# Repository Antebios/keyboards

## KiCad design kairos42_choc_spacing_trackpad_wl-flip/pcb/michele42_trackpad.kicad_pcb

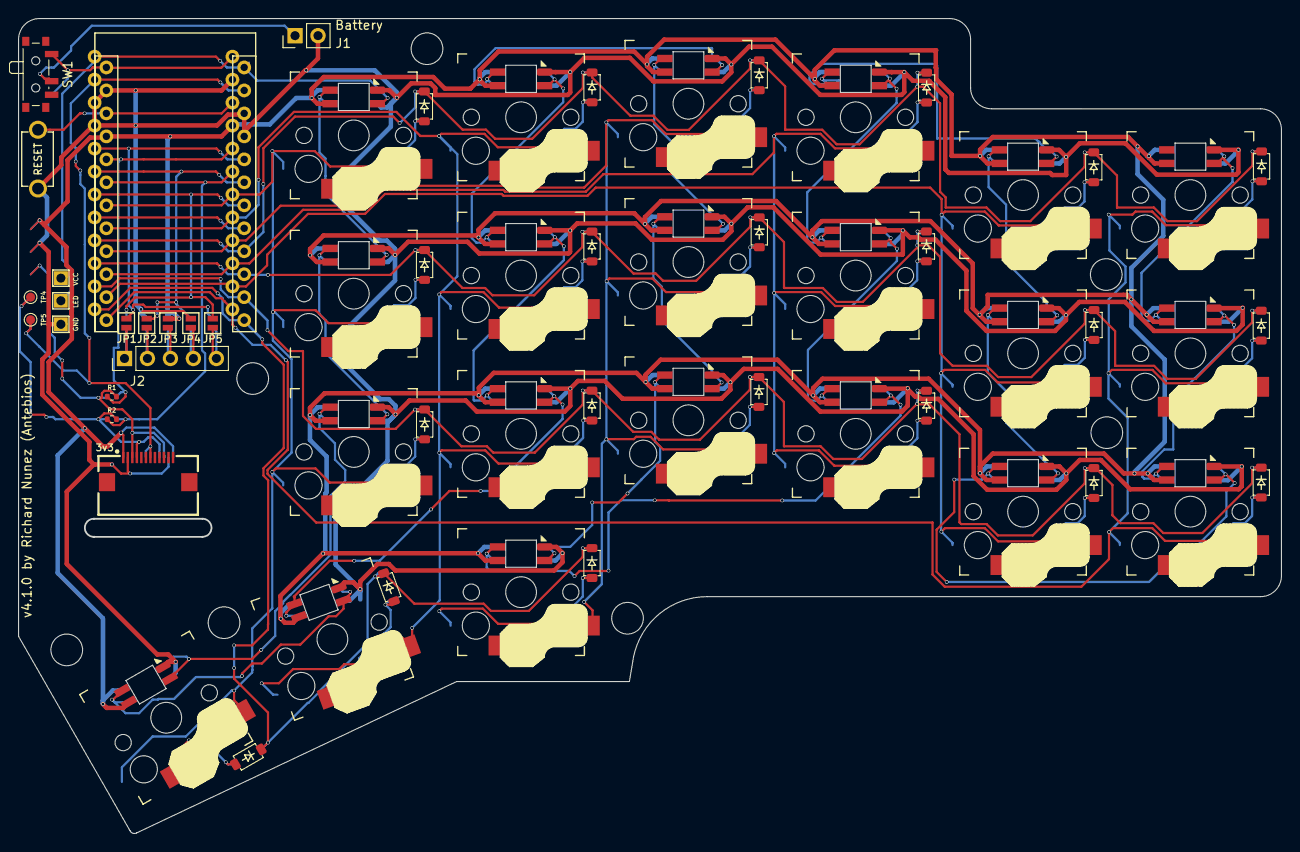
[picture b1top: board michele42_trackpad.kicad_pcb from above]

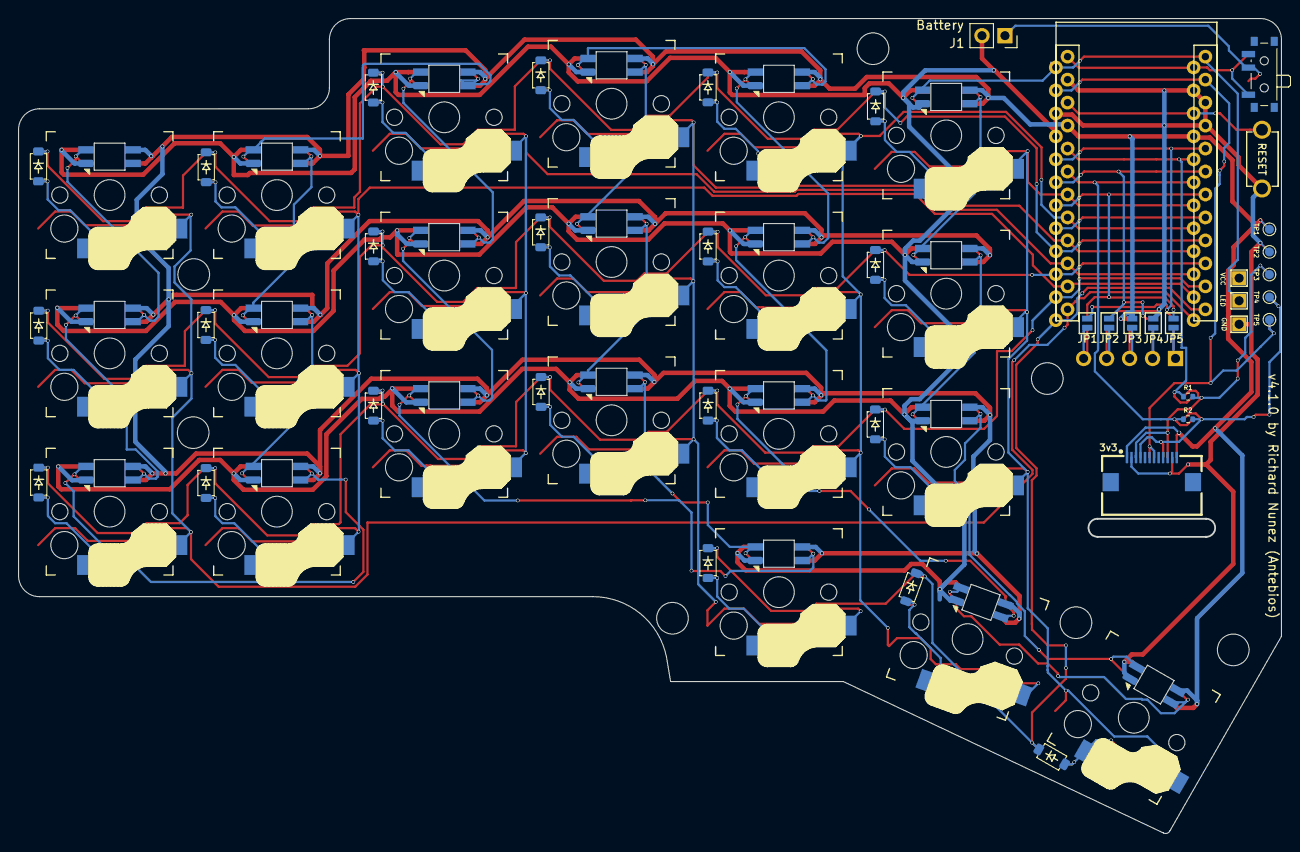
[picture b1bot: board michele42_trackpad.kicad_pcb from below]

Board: 2 copper layers, 139.5 x 90.0 mm, 99 parts (34 on the bottom side), 70 nets.

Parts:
D1, D2, D3, D4, D5, D6, D7, D8, D9, D10, D11, D12, D13, D14, D15, D16, D17, D18, D19, D20, D21: Diode; Diode_SOD-123-double-sided
D22, D23, D24, D25, D26, D27, D28, D29, D30, D31, D32, D33, D34, D35, D36, D37, D38, D39, D40, D41, D42: SK6812MINI-E; SK6812-MINI-E-double-side
H1, H2, H3, H4, H5, H6, H7: Mounting_Hole; MountingHole_3.5mm
J1: Battery; PinHeader_1x02_P2.54mm_Vertical
J2: OLED-5Pin; PinHeader_1x05_P2.54mm_Vertical
J3, J3#2: vik-keyboard-connector-horizontal
J4: LED
JP1, JP1#2, JP2, JP2#2, JP3, JP3#2, JP4, JP4#2, JP5, JP5#2: Jumper; jumper_data-MOD
R1, R1#2, R2, R2#2: 4.7k; R_0402_1005Metric
RSW1: SW_RST; TACT_SWITCH_TVBP06
S1, S2, S3, S4, S5, S6, S7, S8, S9, S10, S11, S12, S13, S14, S15, S16, S17, S18, S19, S20, S21: Keyswitch; Choc_Hotswap-double-sided
SW1: SW_Power; SW_SPDT_PCM12
TP1, TP2, TP3, TP4, TP4#2, TP5, TP5#2: TestPoint; TestPoint_Pad_D1.0mm
U1: MCU_Nice_Nano_V2; ProMicro

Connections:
BATTERY: SW1.1 (A), U1.24 (B+)
CS: JP5.2 (B), JP5#2.2 (B), U1.7 (D4)
Column 0: S1.2, S7.2, S13.2, S19.2, U1.18 (D19)
Column 1: S2.2, S8.2, S14.2, S20.2, U1.17 (D18)
Column 2: S3.2, S9.2, S15.2, S21.2, U1.16 (D15)
Column 3: S4.2, S10.2, S16.2, U1.15 (D14)
Column 4: S5.2, S11.2, S17.2, U1.14 (D16)
Column 5: S6.2, S12.2, S18.2, U1.13 (D10)
DRDY: J3.7 (GP_AD1), J3#2.7 (GP_AD1), TP5.1 (1_1), TP5#2.1 (1_1), U1.2 (D0)
GND: D22.3 (GND), D23.3 (GND), D24.3 (GND), D25.3 (GND), D26.3 (GND), D27.3 (GND), D28.3 (GND), D29.3 (GND), D30.3 (GND), D31.3 (GND), D32.3 (GND), D33.3 (GND), D34.3 (GND), D35.3 (GND), D36.3 (GND), D37.3 (GND), D38.3 (GND), D39.3 (GND), D40.3 (GND), D41.3 (GND), D42.3 (GND), J1.2, J3.2 (GND), J3#2.2 (GND), J4.3, JP4.2 (B), JP4#2.2 (B), RSW1.1, TP2.1 (1_1), U1.3 (GND), U1.4 (GND), U1.23 (GND)
LED: D22.4 (DIN), J4.2, U1.1 (D1)
MOSI: JP1.2 (B), JP1#2.2 (B), U1.5 (D2)
unnamed: D1.2 (A), S1.1
unnamed: D2.2 (A), S2.1
unnamed: D3.2 (A), S3.1
unnamed: D4.2 (A), S4.1
unnamed: D5.2 (A), S5.1
unnamed: D6.2 (A), S6.1
unnamed: D7.2 (A), S7.1
unnamed: D8.2 (A), S8.1
unnamed: D9.2 (A), S9.1
unnamed: D10.2 (A), S10.1
unnamed: D11.2 (A), S11.1
unnamed: D12.2 (A), S12.1
unnamed: D13.2 (A), S13.1
unnamed: D14.2 (A), S14.1
unnamed: D15.2 (A), S15.1
unnamed: D16.2 (A), S16.1
unnamed: D17.2 (A), S17.1
unnamed: D18.2 (A), S18.1
unnamed: D19.2 (A), S19.1
unnamed: D20.2 (A), S20.1
unnamed: D21.2 (A), S21.1
unnamed: D22.2 (DOUT), D28.4 (DIN)
unnamed: D23.4 (DIN), D29.2 (DOUT)
unnamed: D23.2 (DOUT), D24.4 (DIN)
unnamed: D24.2 (DOUT), D30.4 (DIN)
unnamed: D25.4 (DIN), D31.2 (DOUT)
unnamed: D25.2 (DOUT), D26.4 (DIN)
unnamed: D26.2 (DOUT), D32.4 (DIN)
unnamed: D27.4 (DIN), D33.2 (DOUT)
unnamed: D28.2 (DOUT), D34.4 (DIN)
unnamed: D29.4 (DIN), D35.2 (DOUT)
unnamed: D30.2 (DOUT), D36.4 (DIN)
unnamed: D31.4 (DIN), D37.2 (DOUT)
unnamed: D32.2 (DOUT), D38.4 (DIN)
unnamed: D33.4 (DIN), D39.2 (DOUT)
unnamed: D34.2 (DOUT), D40.4 (DIN)
unnamed: D35.4 (DIN), D41.2 (DOUT)
unnamed: D36.2 (DOUT), D42.4 (DIN)
unnamed: D37.4 (DIN), D42.2 (DOUT)
unnamed: D38.2 (DOUT), D39.4 (DIN)
unnamed: D40.2 (DOUT), D41.4 (DIN)
unnamed: J1.1, SW1.2 (B)
unnamed: J2.1, JP1.1 (A), JP5#2.1 (A)
unnamed: J2.2, JP2.1 (A), JP4#2.1 (A)
unnamed: J2.3, JP3.1 (A), JP3#2.1 (A)
unnamed: J2.4, JP2#2.1 (A), JP4.1 (A)
unnamed: J2.5, JP1#2.1 (A), JP5.1 (A)
RESET: RSW1.2, U1.22 (RST)
Row 0: D1.1 (K), D2.1 (K), D3.1 (K), D4.1 (K), D5.1 (K), D6.1 (K), U1.9 (D6)
Row 1: D7.1 (K), D8.1 (K), D9.1 (K), D10.1 (K), D11.1 (K), D12.1 (K), U1.10 (D7)
Row 2: D13.1 (K), D14.1 (K), D15.1 (K), D16.1 (K), D17.1 (K), D18.1 (K), U1.11 (D8)
Row 3: D19.1 (K), D20.1 (K), D21.1 (K), U1.12 (D9)
SCK: JP2.2 (B), JP2#2.2 (B), U1.6 (D3)
SCL: R2.1, R2#2.1, U1.19 (D20)
SDA: R1.1, R1#2.1, U1.20 (D21)
TP-SCL: J3.4 (SCL), J3#2.4 (SCL), R2.2, R2#2.2, TP4.1 (1_1), TP4#2.1 (1_1)
TP-SDA: J3.3 (SDA), J3#2.3 (SDA), R1.2, R1#2.2, TP3.1 (1_1)
VCC: D22.1 (VDD), D23.1 (VDD), D24.1 (VDD), D25.1 (VDD), D26.1 (VDD), D27.1 (VDD), D28.1 (VDD), D29.1 (VDD), D30.1 (VDD), D31.1 (VDD), D32.1 (VDD), D33.1 (VDD), D34.1 (VDD), D35.1 (VDD), D36.1 (VDD), D37.1 (VDD), D38.1 (VDD), D39.1 (VDD), D40.1 (VDD), D41.1 (VDD), D42.1 (VDD), J3.1 (3V3), J3#2.1 (3V3), J4.1, JP3.2 (B), JP3#2.2 (B), TP1.1 (1_1), U1.21 (3.3v)

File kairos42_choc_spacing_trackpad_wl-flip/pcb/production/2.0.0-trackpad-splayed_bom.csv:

Designator,Footprint,Quantity,Value,LCSC Part #
"D1, D10, D11, D12, D13, D14, D15, D16, D17, D18, D19, D2, D20, D21, D22, D3, D4, D5, D6, D7, D8, D9",SK6812-MINI-E-double-side,22,SK6812MINI-E,
"D23, D24, D25, D26, D27, D28, D29, D30, D31, D32, D33, D34, D35, D36, D37, D38, D39, D40, D41, D42, D43, D44",Diode_SOD-123-double-sided,22,Diode,
"H1, H2, H3, H4, H5, H6, H7",MountingHole_3.5mm,7,Mounting_Hole,
J1,PinHeader_1x02_P2.54mm_Vertical,1,Battery,
"J2, J3",vik-keyboard-connector-horizontal,2,~,
J3_2,PinHeader_1x05_P2.54mm_Vertical,1,OLED-5Pin,
J4,LED,1,LED,
"JP1_2, JP1, JP2_2, JP2, JP3_2, JP3, JP4_2, JP4, JP5_2, JP5",jumper_data-MOD,10,Jumper,
"R1_2, R1, R2_2, R2",0402,4,4.7k,
RSW1,TACT_SWITCH_TVBP06,1,SW_RST,
"S1, S10, S11, S12, S13, S14, S15, S16, S17, S18, S19, S2, S20, S21, S22, S3, S4, S5, S6, S7, S8, S9",Choc_Hotswap-double-sided,22,Keyswitch,
SW1,SW_SPDT_PCM12,1,SW_Power,
"TP1_2, TP1, TP2_2, TP2, TP3_2, TP3, TP4_2, TP4, TP5_2, TP5",TestPoint_Pad_D1.0mm,10,TestPoint,
U1,ProMicro,1,MCU_Nice_Nano_V2,

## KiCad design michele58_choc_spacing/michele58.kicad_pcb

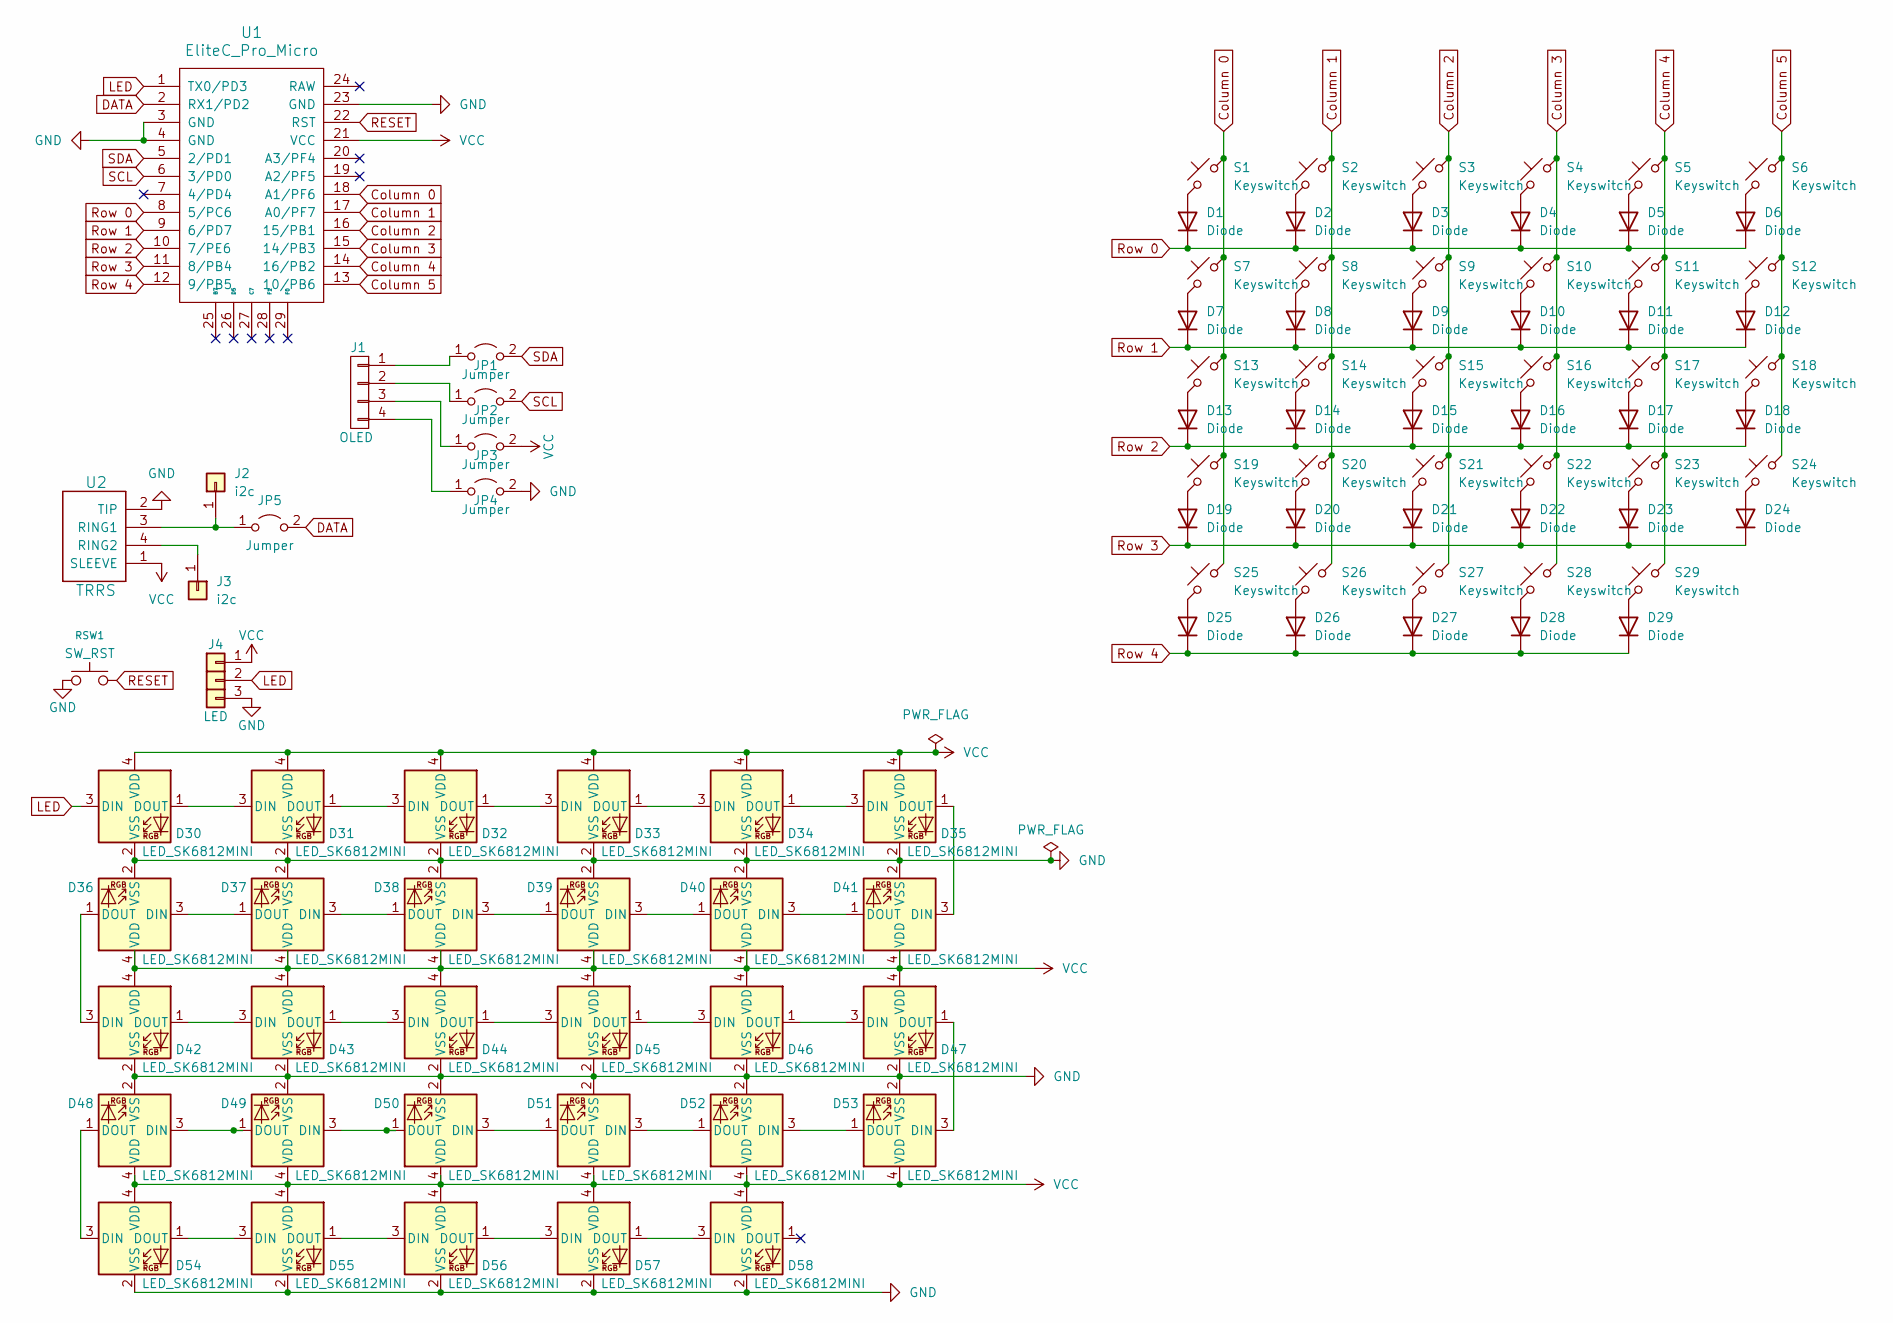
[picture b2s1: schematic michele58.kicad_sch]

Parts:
D1, D2, D3, D4, D5, D6, D7, D8, D9, D10, D11, D12, D13, D14, D15, D16, D17, D18, D19, D20, D21, D22, D23, D24, D25, D26, D27, D28, D29: Diode; Diode_SOD-123
D30, D31, D32, D33, D34, D35, D36, D37, D38, D39, D40, D41, D42, D43, D44, D45, D46, D47, D48, D49, D50, D51, D52, D53, D54, D55, D56, D57, D58: LED_SK6812MINI; LED_SK6812MINI-MOD1
J1: OLED; OLED_4Pin
J2, J3: i2c; 1pin_conn
J4: LED
JP1, JP2, JP3, JP4, JP5: Jumper; jumper_data-MOD
RSW1: SW_RST; TACT_SWITCH_TVBP06
S1, S2, S3, S4, S5, S6, S7, S8, S9, S10, S11, S12, S13, S14, S15, S16, S17, S18, S19, S20, S21, S22, S23, S24, S25, S26, S27, S28, S29: Keyswitch; SW_Kailh_Choc_V1_1.00u
U1: EliteC_Pro_Micro; Elite-C
U2: TRRS; TRRS_PJ-320A

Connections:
Column 0: S1.2, S7.2, S13.2, S19.2, S25.2, U1.18 (A1/PF6)
Column 1: S2.2, S8.2, S14.2, S20.2, S26.2, U1.17 (A0/PF7)
Column 2: S3.2, S9.2, S15.2, S21.2, S27.2, U1.16 (15/PB1)
Column 3: S4.2, S10.2, S16.2, S22.2, S28.2, U1.15 (14/PB3)
Column 4: S5.2, S11.2, S17.2, S23.2, S29.2, U1.14 (16/PB2)
Column 5: S6.2, S12.2, S18.2, S24.2, U1.13 (10/PB6)
DATA: JP5.2 (B), U1.2 (RX1/PD2)
GND: D30.2 (VSS), D31.2 (VSS), D32.2 (VSS), D33.2 (VSS), D34.2 (VSS), D35.2 (VSS), D36.2 (VSS), D37.2 (VSS), D38.2 (VSS), D39.2 (VSS), D40.2 (VSS), D41.2 (VSS), D42.2 (VSS), D43.2 (VSS), D44.2 (VSS), D45.2 (VSS), D46.2 (VSS), D47.2 (VSS), D48.2 (VSS), D49.2 (VSS), D50.2 (VSS), D51.2 (VSS), D52.2 (VSS), D53.2 (VSS), D54.2 (VSS), D55.2 (VSS), D56.2 (VSS), D57.2 (VSS), D58.2 (VSS), J4.3, JP4.2 (B), RSW1.1, U1.3 (GND), U1.4 (GND), U1.23 (GND), U2.2 (TIP)
LED: D30.3 (DIN), J4.2, U1.1 (TX0/PD3)
unnamed: D1.2 (A), S1.1
unnamed: D2.2 (A), S2.1
unnamed: D3.2 (A), S3.1
unnamed: D4.2 (A), S4.1
unnamed: D5.2 (A), S5.1
unnamed: D6.2 (A), S6.1
unnamed: D7.2 (A), S7.1
unnamed: D8.2 (A), S8.1
unnamed: D9.2 (A), S9.1
unnamed: D10.2 (A), S10.1
unnamed: D11.2 (A), S11.1
unnamed: D12.2 (A), S12.1
unnamed: D13.2 (A), S13.1
unnamed: D14.2 (A), S14.1
unnamed: D15.2 (A), S15.1
unnamed: D16.2 (A), S16.1
unnamed: D17.2 (A), S17.1
unnamed: D18.2 (A), S18.1
unnamed: D19.2 (A), S19.1
unnamed: D20.2 (A), S20.1
unnamed: D21.2 (A), S21.1
unnamed: D22.2 (A), S22.1
unnamed: D23.2 (A), S23.1
unnamed: D24.2 (A), S24.1
unnamed: D25.2 (A), S25.1
unnamed: D26.2 (A), S26.1
unnamed: D27.2 (A), S27.1
unnamed: D28.2 (A), S28.1
unnamed: D29.2 (A), S29.1
unnamed: D30.1 (DOUT), D31.3 (DIN)
unnamed: D31.1 (DOUT), D32.3 (DIN)
unnamed: D32.1 (DOUT), D33.3 (DIN)
unnamed: D33.1 (DOUT), D34.3 (DIN)
unnamed: D34.1 (DOUT), D35.3 (DIN)
unnamed: D35.1 (DOUT), D41.3 (DIN)
unnamed: D36.3 (DIN), D37.1 (DOUT)
unnamed: D36.1 (DOUT), D42.3 (DIN)
unnamed: D37.3 (DIN), D38.1 (DOUT)
unnamed: D38.3 (DIN), D39.1 (DOUT)
unnamed: D39.3 (DIN), D40.1 (DOUT)
unnamed: D40.3 (DIN), D41.1 (DOUT)
unnamed: D42.1 (DOUT), D43.3 (DIN)
unnamed: D43.1 (DOUT), D44.3 (DIN)
unnamed: D44.1 (DOUT), D45.3 (DIN)
unnamed: D45.1 (DOUT), D46.3 (DIN)
unnamed: D46.1 (DOUT), D47.3 (DIN)
unnamed: D47.1 (DOUT), D53.3 (DIN)
unnamed: D48.3 (DIN), D49.1 (DOUT)
unnamed: D48.1 (DOUT), D54.3 (DIN)
unnamed: D49.3 (DIN), D50.1 (DOUT)
unnamed: D50.3 (DIN), D51.1 (DOUT)
unnamed: D51.3 (DIN), D52.1 (DOUT)
unnamed: D52.3 (DIN), D53.1 (DOUT)
unnamed: D54.1 (DOUT), D55.3 (DIN)
unnamed: D55.1 (DOUT), D56.3 (DIN)
unnamed: D56.1 (DOUT), D57.3 (DIN)
unnamed: D57.1 (DOUT), D58.3 (DIN)
unnamed: J1.1, JP1.1 (A)
unnamed: J1.2, JP2.1 (A)
unnamed: J1.3, JP3.1 (A)
unnamed: J1.4, JP4.1 (A)
unnamed: J2.1, JP5.1 (A), U2.3 (RING1)
unnamed: J3.1, U2.4 (RING2)
RESET: RSW1.2, U1.22 (RST)
Row 0: D1.1 (K), D2.1 (K), D3.1 (K), D4.1 (K), D5.1 (K), D6.1 (K), U1.8 (5/PC6)
Row 1: D7.1 (K), D8.1 (K), D9.1 (K), D10.1 (K), D11.1 (K), D12.1 (K), U1.9 (6/PD7)
Row 2: D13.1 (K), D14.1 (K), D15.1 (K), D16.1 (K), D17.1 (K), D18.1 (K), U1.10 (7/PE6)
Row 3: D19.1 (K), D20.1 (K), D21.1 (K), D22.1 (K), D23.1 (K), D24.1 (K), U1.11 (8/PB4)
Row 4: D25.1 (K), D26.1 (K), D27.1 (K), D28.1 (K), D29.1 (K), U1.12 (9/PB5)
SCL: JP2.2 (B), U1.6 (3/PD0)
SDA: JP1.2 (B), U1.5 (2/PD1)
VCC: D30.4 (VDD), D31.4 (VDD), D32.4 (VDD), D33.4 (VDD), D34.4 (VDD), D35.4 (VDD), D36.4 (VDD), D37.4 (VDD), D38.4 (VDD), D39.4 (VDD), D40.4 (VDD), D41.4 (VDD), D42.4 (VDD), D43.4 (VDD), D44.4 (VDD), D45.4 (VDD), D46.4 (VDD), D47.4 (VDD), D48.4 (VDD), D49.4 (VDD), D50.4 (VDD), D51.4 (VDD), D52.4 (VDD), D53.4 (VDD), D54.4 (VDD), D55.4 (VDD), D56.4 (VDD), D57.4 (VDD), D58.4 (VDD), J4.1, JP3.2 (B), U1.21 (VCC), U2.1 (SLEEVE)

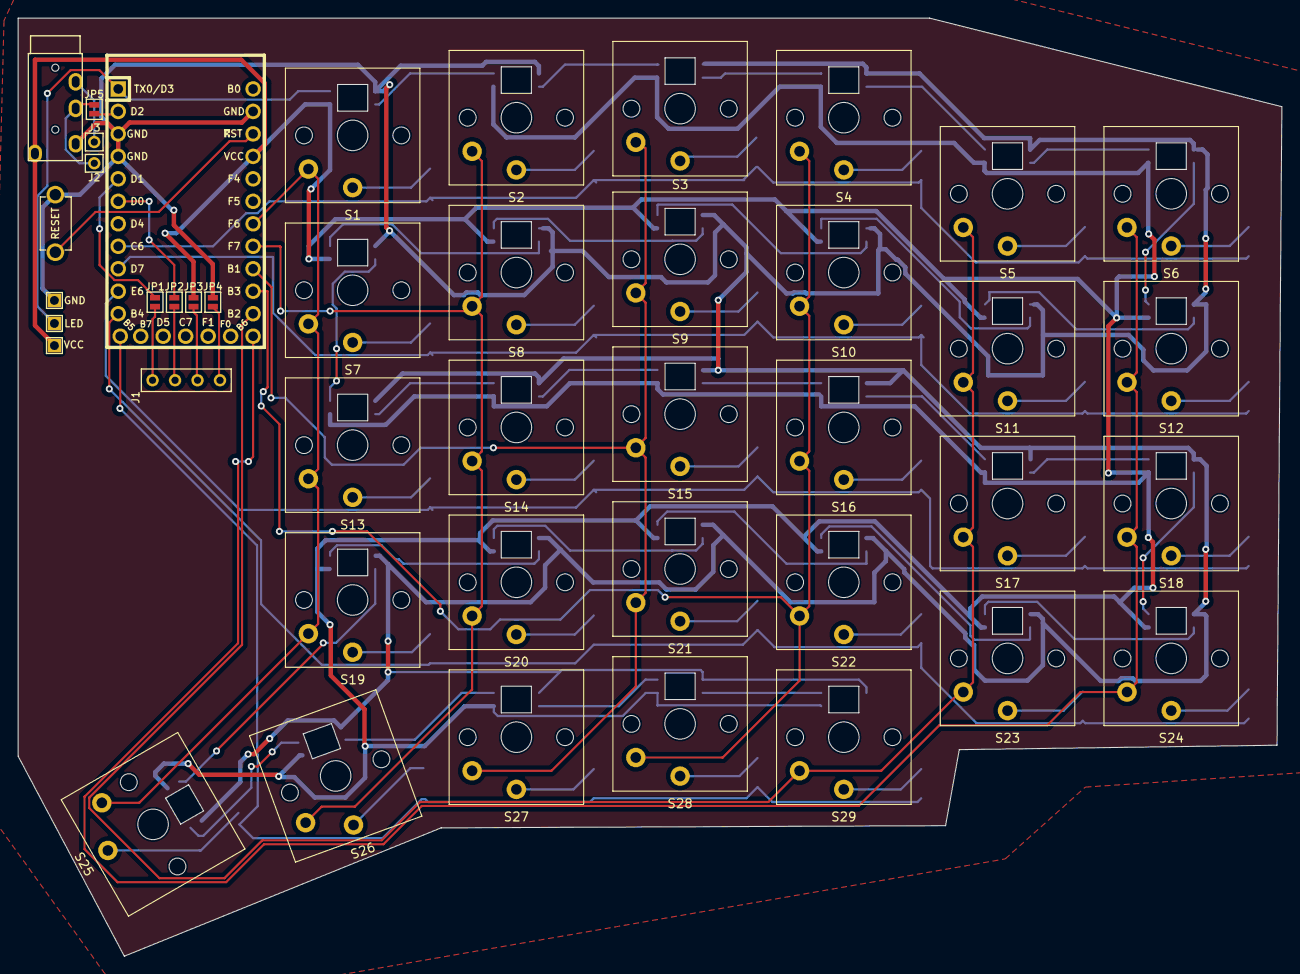
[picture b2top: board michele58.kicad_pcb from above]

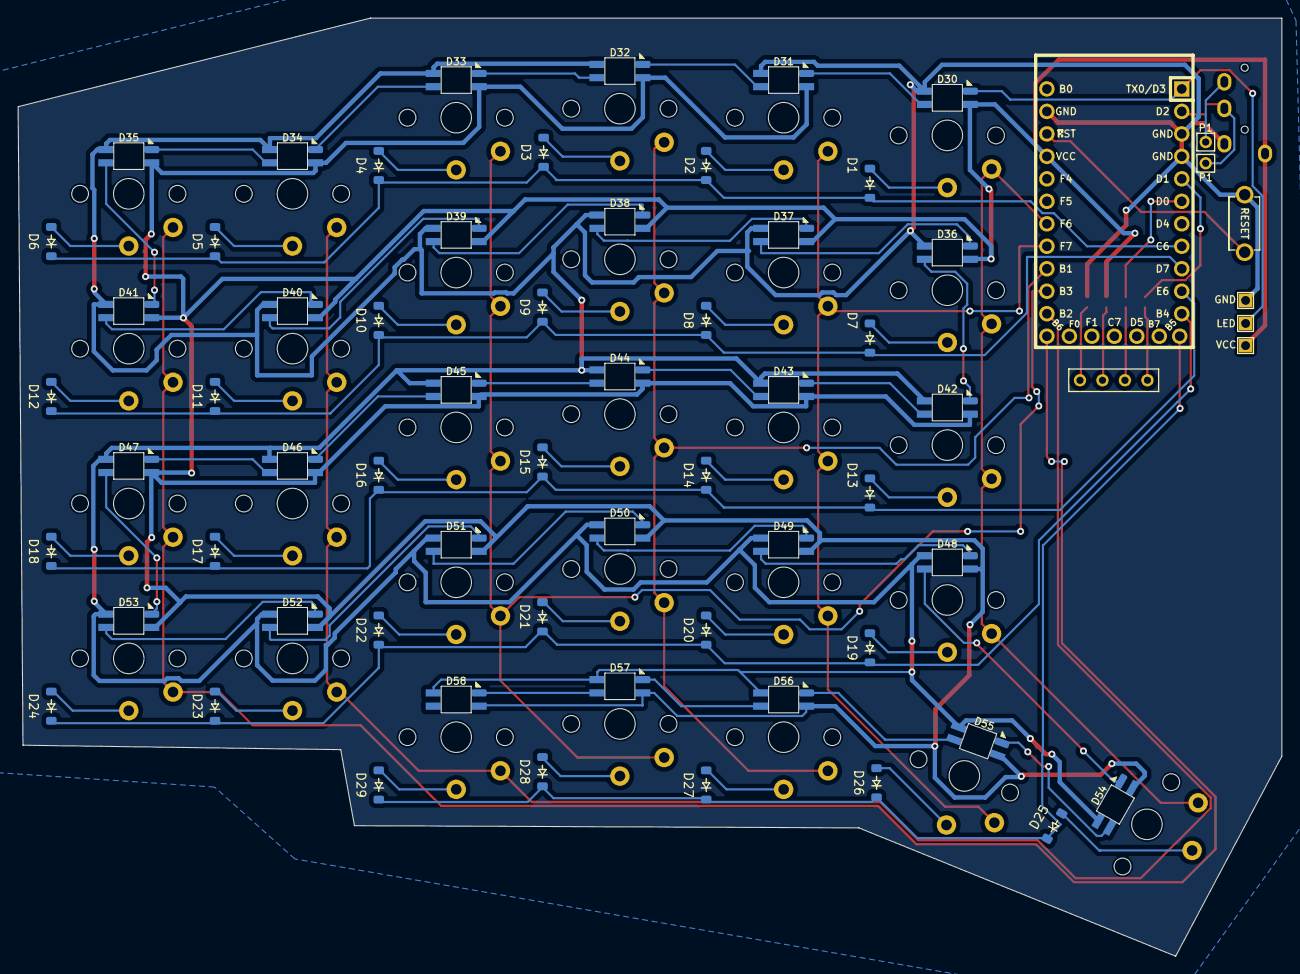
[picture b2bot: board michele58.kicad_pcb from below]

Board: 2 copper layers, 142.8 x 106.0 mm, 99 parts (29 on the bottom side), 81 nets.

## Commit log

2024-01-25 all changes
2024-01-27 latest changes
2024-01-29 more tweaks
2024-01-29 fixes
2024-01-29 Add new footprints
2024-01-29 Moved files.
2024-01-29 Created a plate and stl to prinnt
2024-01-30 first gerber files
2024-01-31 add bottom plate of case
2024-03-04 Made mounting holes larger, added mask, and add STL for bottom case with spacers.
2024-03-04 adding readme
2024-11-27 Add Wireless RGB keyboard with thumb sticks
2024-11-27 Add more 48 changes, not final
2024-11-27 Add 58 images
2024-11-30 Small fixes and images
2024-12-01 Relocate mounting holes to make room for battery
2024-12-02 create case and mounting plate
2026-05-04 Add kairos with cirque trackpad
2026-05-05 Resolve DRC errors
2026-05-05 Trackpad cas stuff - wip
2026-06-06 Trackpad cas stuff - wip again
